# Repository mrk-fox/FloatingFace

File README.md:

<div align="center">
<h1>FloatingFace</h1><br>
  
A three-string-mounted small multifunctional cable roboter concept. <br>

<br>

<div align="left">v1.0 aka "Floaty"</div>
</div>
<br>

FloatingFace is a roboter, mounted by 3mm paracord ropes at three points arranged in a triangle which achieves movement withing and under these 3 mounting points by tensioning or loosening each these ropes.

## Key features

- 3-points mount
- cheeseplate with additional servo for mechanization
- automatic calibration
- custom driver PCB with three TMC2209 slots
- redundant visual and magnetic travel distance encoder
- AS5600 magnetic encoders
- MPU5060
- possibility for rope pulley if higher loads applied

I built this project as proof-of-concept system for a 3-point-mounted, portable cable roboter with an universal extensions interface.

## PCB

Floaty has a custom-designed driver developer board for three TMC2209 drivers. Look at the design! <br>

Thats all the layers overlapped...
<br><br><br>

...and thats the front design. There is nothing on the back
<br><br><br>

## Schematic
<br>
The overview schematic implementing a TCA9548 for the I2C controll of the three AS5600 sensors looks like this:

and that is the schematic for the delta_drive v1.1:

https://github.com/mrk-fox/FloatingFace/blob/main/pictures/delta_drive_v1.1_schematic.png

## Math
The basics were worked out with simple linear algebra, which are explained in this video together with the calibration process:

[The math behind "Floaty", the cable roboter](https://youtu.be/A8Sq22G1rsY)

Further, to make the implementation easier, all the calculation were modelled in Simulink:

<br>

The movement algorithm itself works on command through these steps:
1. Validate coordinates
2. Calculate $\Delta(g_n)$ (individual motor run vectors)
3. Calculate time-based movement coefficients $c(\Delta(g_n))$
4. Move in accordance to coefficitens slowly until all motor sensors register rising edge on light sensor
5. Re-calculate path
6. Move fast using PCNT counters
7. Slow down 2 guide sensor revolutions before movement finish
8. Proceed until finish on magnetic encoders feedback
9. Calibrate angles on finish

For angle calibration, Floaty uses the MP5060 sensor which gives an angle relative to gravity and the direction of the orthogonal of the angled face of the sensor. With that data an iterative funciton is started ajusting one motor step at a time until an angle less than 10 degrees is reached. 

## Assembly
The assembly is currently a prediciton of the possible steps. I doubt, that anyone will build this before me, but here we go:

1. Begin with the level one baseplate assemble the motors with the line drums and place them onto the baseplate
2. Mount the Servo and the MCU to the motor mount and baseplate
3. Assemble the 20x20 frame hexagon and mount the baseplate to the hexagon together with the line guides/sensing units
4. Assemble the secon level (electronics) and connect all electronics! (see below)
5. Fix everything together with the threaded rods and the spacers
6. Add the cheeseplate
7. Flash the firmware

## Cables

As the size of the robot is constrainted to certain limits, cable routing is crutial to ensure a safe and reliable operation. The following rules apply:
1. Zip-ties packaging the cable strands shoukd be placed every 2cm (0.787in)
2. Every cable leading to the line measurment units/motos should be placed in the through-leading holes of the appropriate third of the robot
3. A safe-zone of 1cm (0.393in) around the perimeter of the cutout of the basement plate for the line rolls should be cable-free to ensure a tangle-free operation
The mounting is done through running zip ties around the vertical spacers for the levels and the cable holes on the baseplates themselves.

## Zine Page

## Credit
I thank this project to... <br>
... [KiCad](https://www.kicad.org/)<br>
... [HackClub Fallout](https://fallout.hackclub.com/)<br>
... [Autodesk Inventor](https://www.autodesk.com/de/products/inventor/overview)<br>
... [BenjaminW](https://www.thingiverse.com/BenjaminW/designs) and [Serj Minin](https://grabcad.com/serj.minin-1) for the models

## License

This hardware project is licensed under the **CERN Open Hardware Licence v2 - Strongly Reciprocal (CERN-OHL-S)**.

See the [LICENSE](./LICENSE) file for details, or visit https://ohwr.org/cern_ohl_s_v2.

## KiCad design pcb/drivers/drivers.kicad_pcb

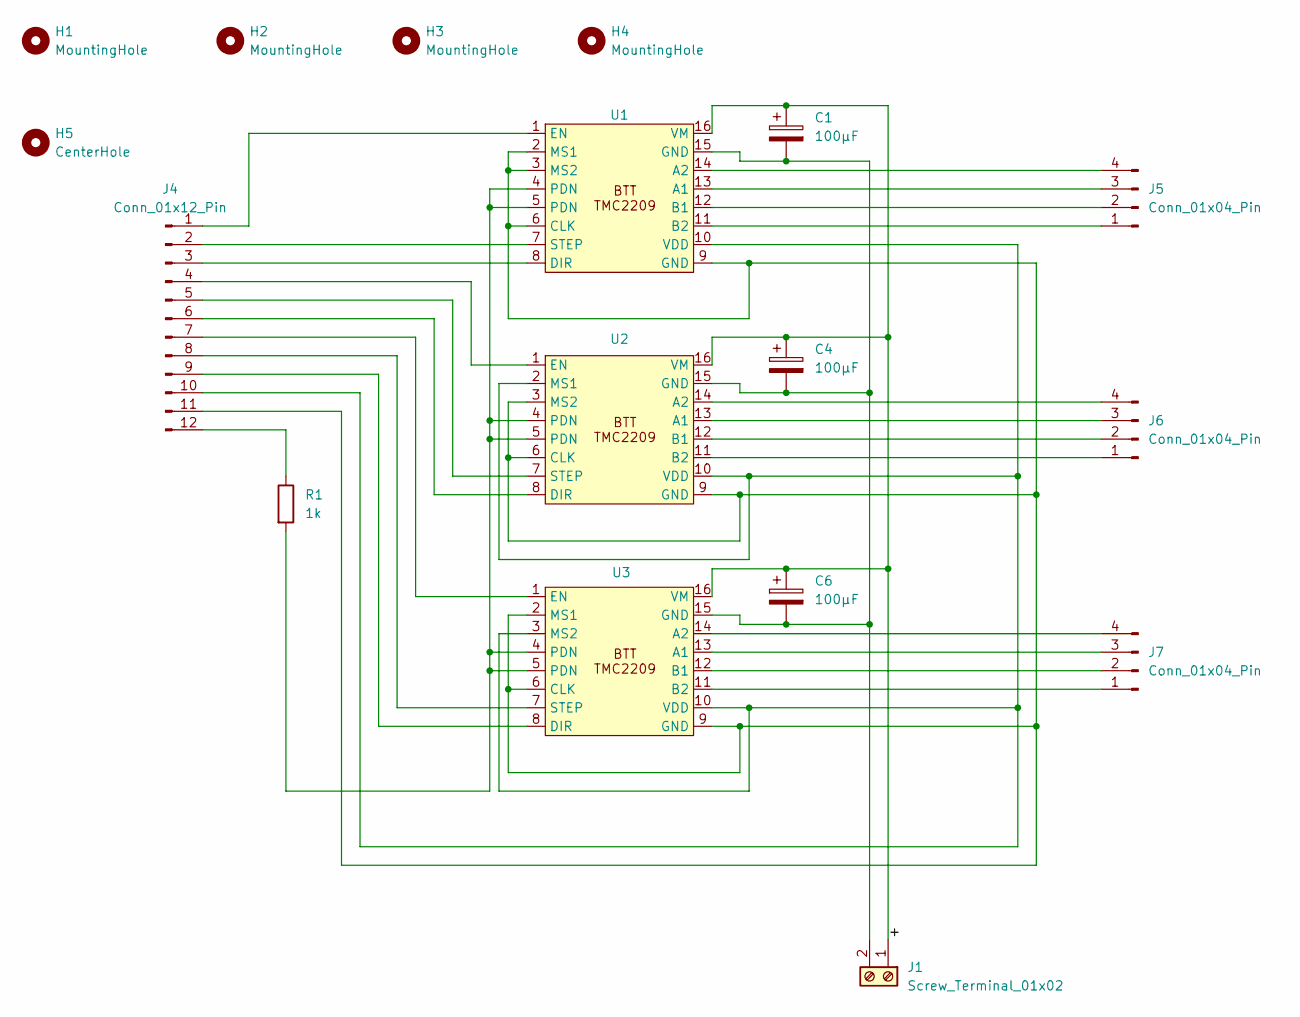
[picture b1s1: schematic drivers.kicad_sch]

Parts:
C1, C4, C6: 100µF; CP_Radial_D8.0mm_P5.00mm
H1, H2, H3, H4: MountingHole; MountingHole_3.2mm_M3
H5: CenterHole; MountingHole_5.3mm_M5_ISO7380
J1: Screw_Terminal_01x02; TerminalBlock_Phoenix_MKDS-1,5-2-5.08_1x02_P5.08mm_Horizont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
J4: Conn_01x12_Pin; PinHeader_1x12_P2.54mm_Vertical
J5, J6, J7: Conn_01x04_Pin; PinHeader_1x04_P2.54mm_Vertical
R1: 1k; R_Axial_DIN0207_L6.3mm_D2.5mm_P10.16mm_Horizontal
U1, U2, U3: TMC2209-Breakout

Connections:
/+: C1.1, C4.1, C6.1, J1.1, U1.16 (VM), U2.16 (VM), U3.16 (VM)
unnamed: C1.2, C4.2, C6.2, J1.2, U1.15 (GND), U2.15 (GND), U3.15 (GND)
unnamed: J4.1, U1.1 (EN)
unnamed: J4.2, U1.7 (STEP)
unnamed: J4.3, U1.8 (DIR)
unnamed: J4.4, U2.1 (EN)
unnamed: J4.5, U2.7 (STEP)
unnamed: J4.6, U2.8 (DIR)
unnamed: J4.7, U3.1 (EN)
unnamed: J4.8, U3.7 (STEP)
unnamed: J4.9, U3.8 (DIR)
unnamed: J4.10, U1.10 (VDD), U2.2 (MS1), U2.10 (VDD), U3.3 (MS2), U3.10 (VDD)
unnamed: J4.11, U1.2 (MS1), U1.3 (MS2), U1.6 (CLK), U1.9 (GND), U2.3 (MS2), U2.6 (CLK), U2.9 (GND), U3.2 (MS1), U3.6 (CLK), U3.9 (GND)
unnamed: J4.12, R1.1
unnamed: J5.1, U1.11 (B2)
unnamed: J5.2, U1.12 (B1)
unnamed: J5.3, U1.13 (A1)
unnamed: J5.4, U1.14 (A2)
unnamed: J6.1, U2.11 (B2)
unnamed: J6.2, U2.12 (B1)
unnamed: J6.3, U2.13 (A1)
unnamed: J6.4, U2.14 (A2)
unnamed: J7.1, U3.11 (B2)
unnamed: J7.2, U3.12 (B1)
unnamed: J7.3, U3.13 (A1)
unnamed: J7.4, U3.14 (A2)
unnamed: R1.2, U1.4 (PDN), U1.5 (PDN), U2.4 (PDN), U2.5 (PDN), U3.4 (PDN), U3.5 (PDN)

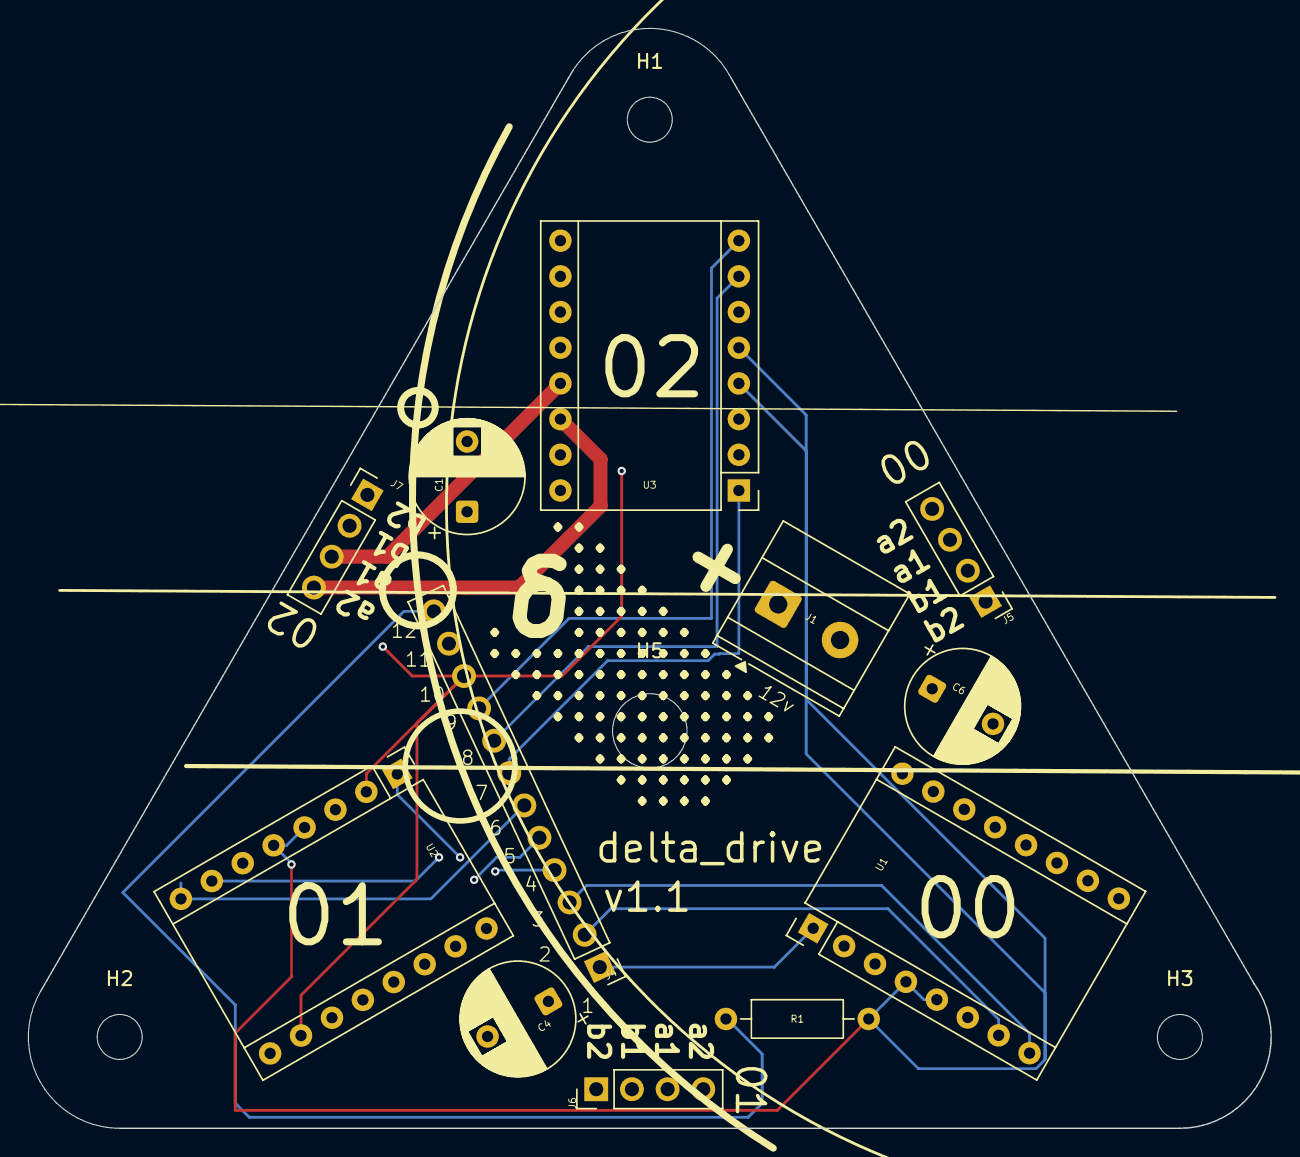
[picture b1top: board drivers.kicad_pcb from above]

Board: 4 copper layers, 88.4 x 78.3 mm, 17 parts (0 on the bottom side), 27 nets.

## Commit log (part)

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2026-03-24 Fist Baseplate Design
    First Baseplate design with an ESP32-S3 for reference and one NEMA17 Motor mounted
2026-03-25 DevSession No.3
2026-03-29 v0.1
2026-03-31 v0.2
2026-04-01 v0.4
2026-04-01 updated programming v0.4
2026-04-02 Docs work No 1
2026-04-02 Fixed Simulink error
2026-04-02 Documantary changes of the PCBs
2026-04-02 CERN License added
2026-04-02 Revise README with detailed project information
    Expanded project description and added key features, PCB, schematic, math, and credits sections.
2026-04-02 A little bit of this, a little bit of that ahhhh commit
2026-04-02 Added Zine
2026-04-02 Small changes again
2026-04-02 Remove header row from BOM.csv
    Removed the header row from BOM.csv and adjusted the data accordingly.
2026-04-02 Correct BOM added
2026-04-03 Update README with FloatingFace description
    Added a description of FloatingFace's movement mechanism.
2026-04-03 Added precise and correct BOM
2026-04-24 Added .pdf fallout zine
2026-05-03 Update README with cable routing rules
    Added cable routing guidelines for robot assembly.
2026-05-05 zine_page updated
2026-05-05 Update cable routing instructions in README
    Added instructions for cable mounting using zip ties.
2026-05-08 Add assembly section to README
    Added assembly instructions for the robot build process.

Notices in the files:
README.md:
License: CERN-OHL-S
